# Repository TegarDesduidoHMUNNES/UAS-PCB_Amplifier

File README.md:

-Tegar Desduido Hasbing Mulia
--2305110008
---Teknik Komputer 2023
----Matkul Elektronika-UAS

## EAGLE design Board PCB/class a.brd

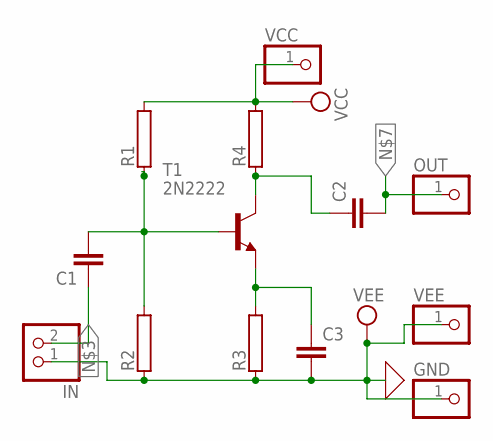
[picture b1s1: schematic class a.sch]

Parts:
C1, C2, C3: C2,5-3; C2.5-3
GND: PINHD-1X1; 1X01
IN: PINHD-1X2; 1X02
OUT: PINHD-1X1; 1X01
R1, R2, R3, R4: RAC01; AC01
T1: 2N2222; TO18
VCC: PINHD-1X1; 1X01
VEE: PINHD-1X1; 1X01

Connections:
unnamed: C1.2, R1.1, R2.2, T1.2 (B)
unnamed: C2.1, R4.1, T1.3 (C)
unnamed: C1.1, IN.2
unnamed: C3.1, R3.2, T1.1 (E)
unnamed: C2.2, OUT.1
VCC: R1.2, R4.2, VCC.1
VEE: C3.2, GND.1, IN.1, R2.1, R3.1, VEE.1

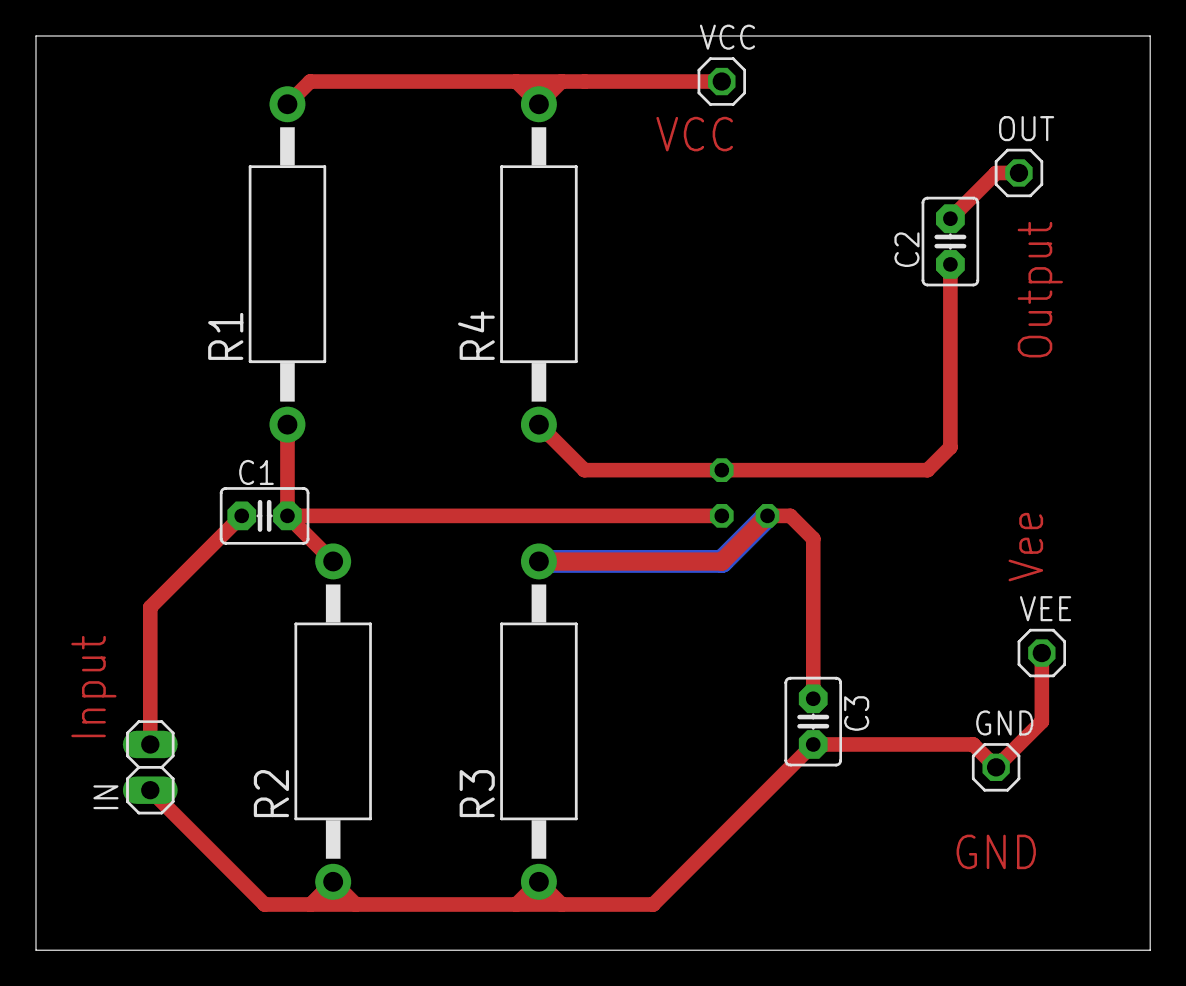
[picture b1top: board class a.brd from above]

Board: 2 copper layers, 61.9 x 50.8 mm, 13 parts (1 on the bottom side), 7 nets.

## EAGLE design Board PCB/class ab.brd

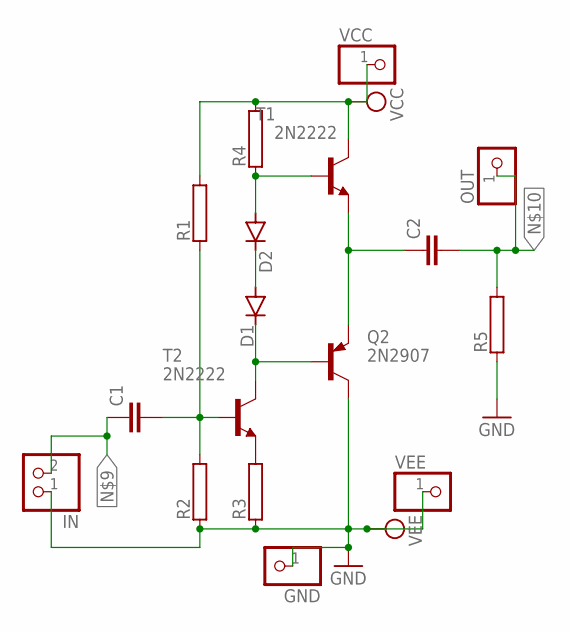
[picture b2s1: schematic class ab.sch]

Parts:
C1, C2: C2,5-3; C2.5-3
D1, D2: 1N4148DO35-7; DO35-7
GND: PINHD-1X1; 1X01
IN: PINHD-1X2; 1X02
OUT: PINHD-1X1; 1X01
Q2: 2N2907; TO18
R1, R2, R3, R4, R5: RAC01; AC01
T1, T2: 2N2222; TO18
VCC: PINHD-1X1; 1X01
VEE: PINHD-1X1; 1X01

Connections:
GND: GND.1, IN.1, Q2.3 (C), R2.1, R3.1, R5.1, VEE.1
unnamed: C1.2, R1.1, R2.2, T2.2 (B)
unnamed: D1.C, Q2.2 (B), T2.3 (C)
unnamed: D1.A, D2.C
unnamed: D2.A, R4.1, T1.2 (B)
unnamed: R3.2, T2.1 (E)
unnamed: C2.1, Q2.1 (E), T1.1 (E)
unnamed: C1.1, IN.2
unnamed: C2.2, OUT.1, R5.2
VCC: R1.2, R4.2, T1.3 (C), VCC.1

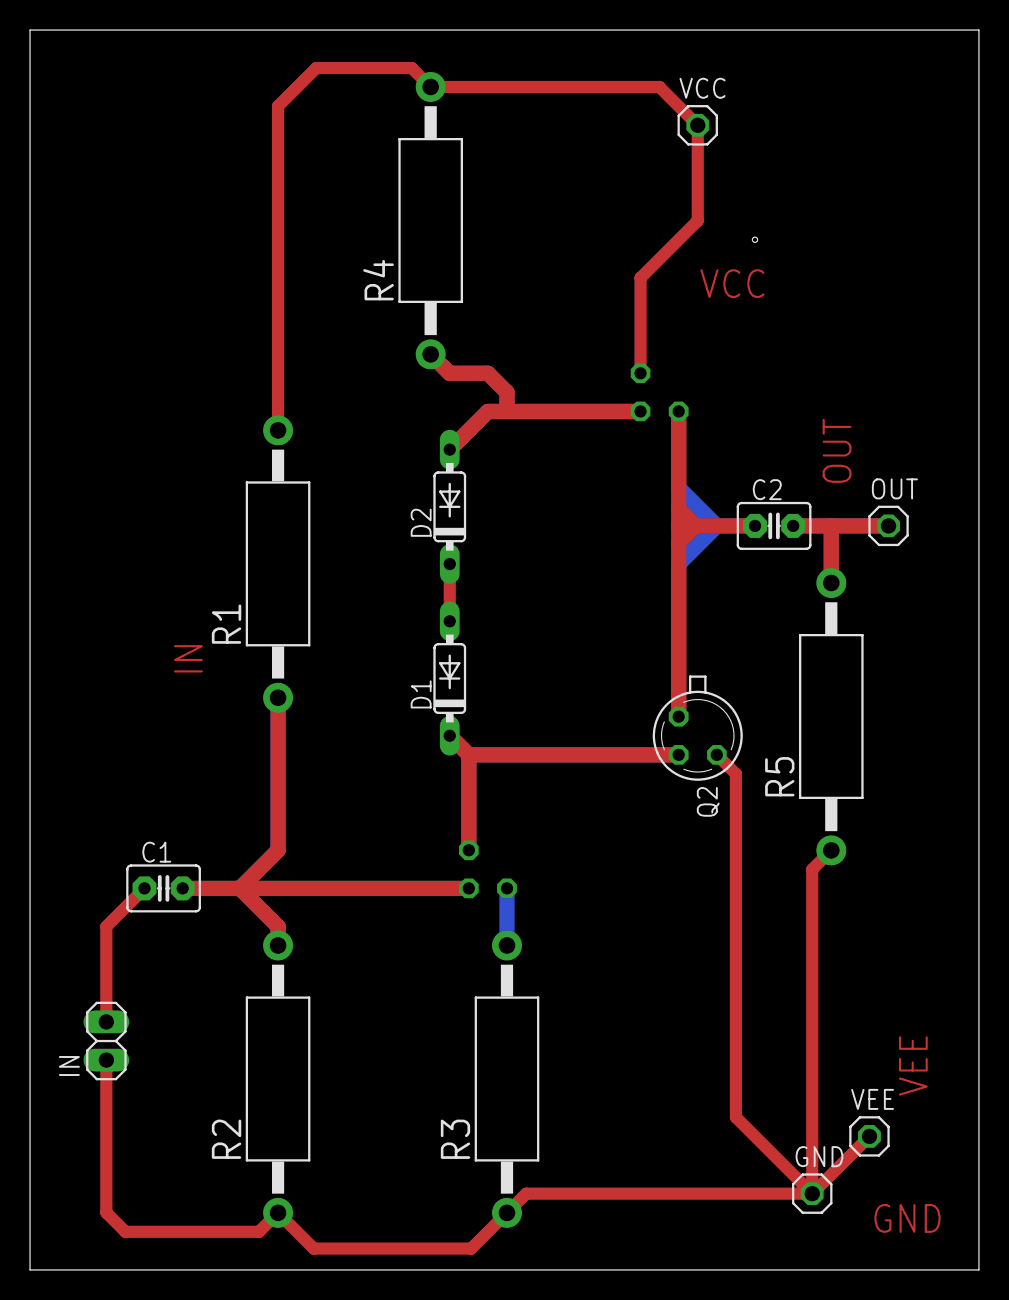
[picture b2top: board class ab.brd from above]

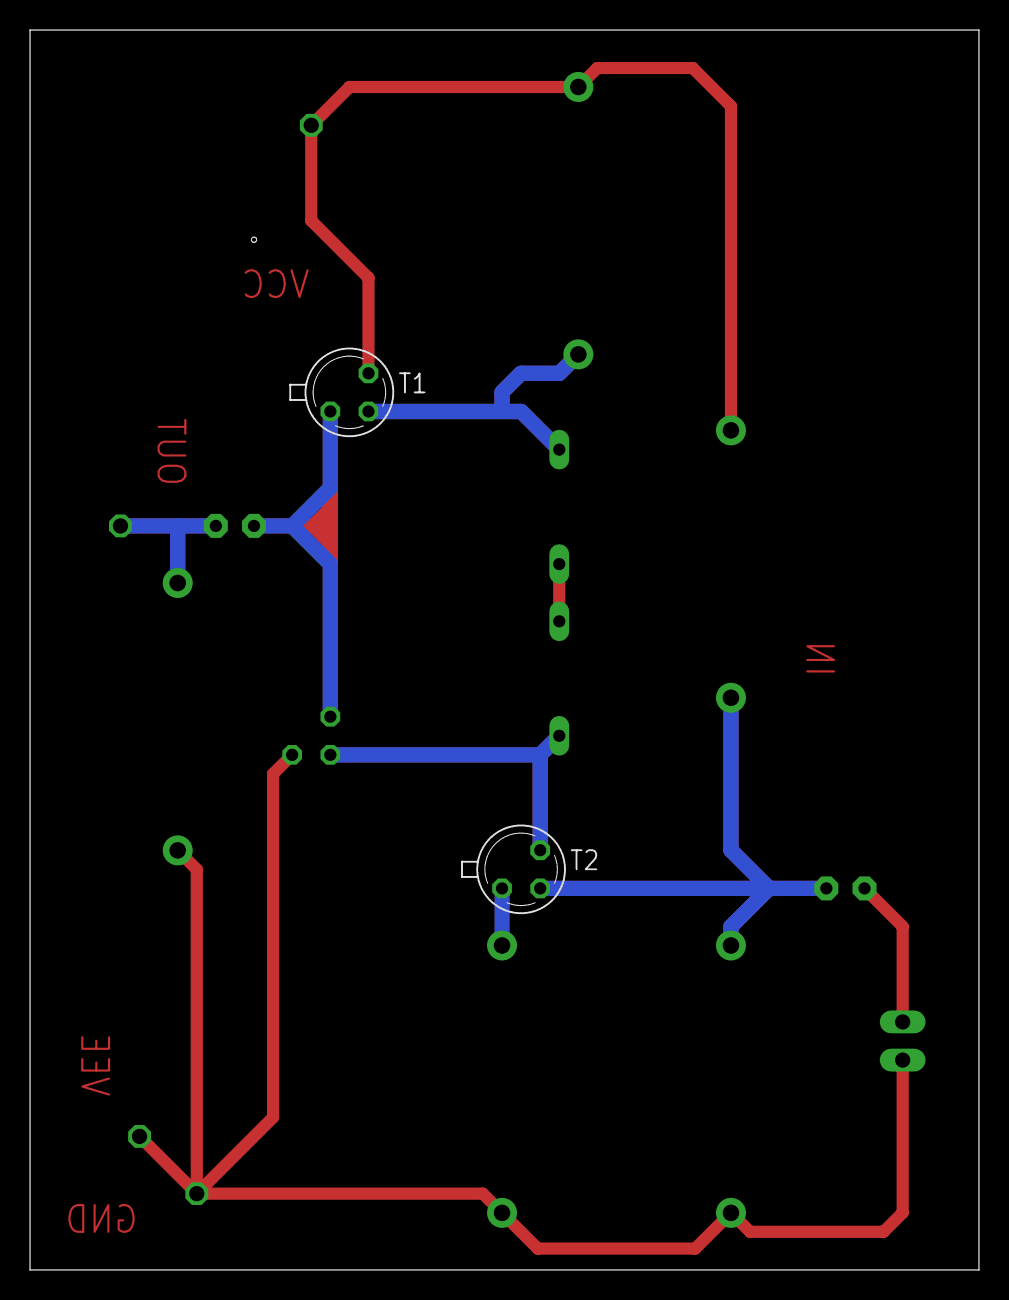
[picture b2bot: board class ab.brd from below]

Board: 2 copper layers, 63.2 x 82.5 mm, 17 parts (2 on the bottom side), 10 nets.

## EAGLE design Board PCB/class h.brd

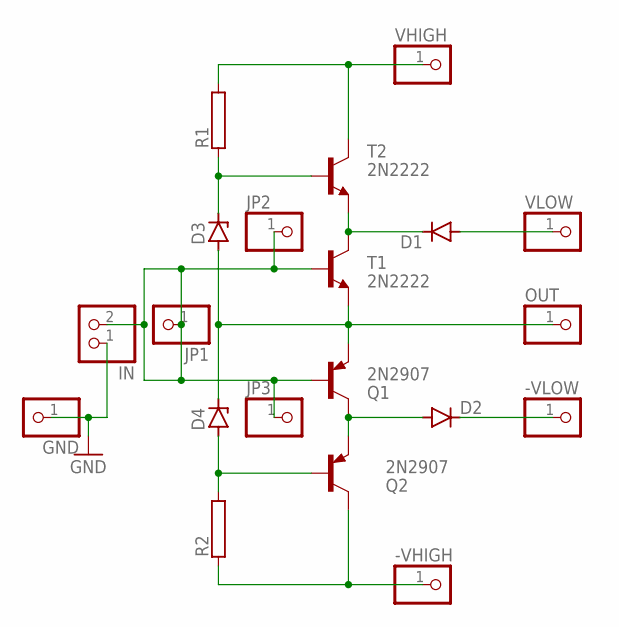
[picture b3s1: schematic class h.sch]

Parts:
-VHIGH: PINHD-1X1; 1X01
-VLOW: PINHD-1X1; 1X01
D1, D2: 1N4148DO35-7; DO35-7
D3, D4: 1N4728; DO41Z10
GND: PINHD-1X1; 1X01
IN: PINHD-1X2; 1X02
JP1, JP2, JP3: PINHD-1X1; 1X01
OUT: PINHD-1X1; 1X01
Q1, Q2: 2N2907; TO18
R1, R2: RAC01; AC01
T1, T2: 2N2222; TO18
VHIGH: PINHD-1X1; 1X01
VLOW: PINHD-1X1; 1X01

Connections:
GND: GND.1, IN.1
unnamed: D3.C, R1.1, T2.2 (B)
unnamed: IN.2, JP1.1, JP2.1, JP3.1, Q1.2 (B), T1.2 (B)
unnamed: D1.A, VLOW.1
unnamed: D3.A, D4.C, OUT.1, Q1.1 (E), T1.1 (E)
unnamed: D1.C, T1.3 (C), T2.1 (E)
unnamed: D2.A, Q1.3 (C), Q2.1 (E)
unnamed: -VHIGH.1, Q2.3 (C), R2.1
unnamed: R1.2, T2.3 (C), VHIGH.1
unnamed: D4.A, Q2.2 (B), R2.2
unnamed: -VLOW.1, D2.C

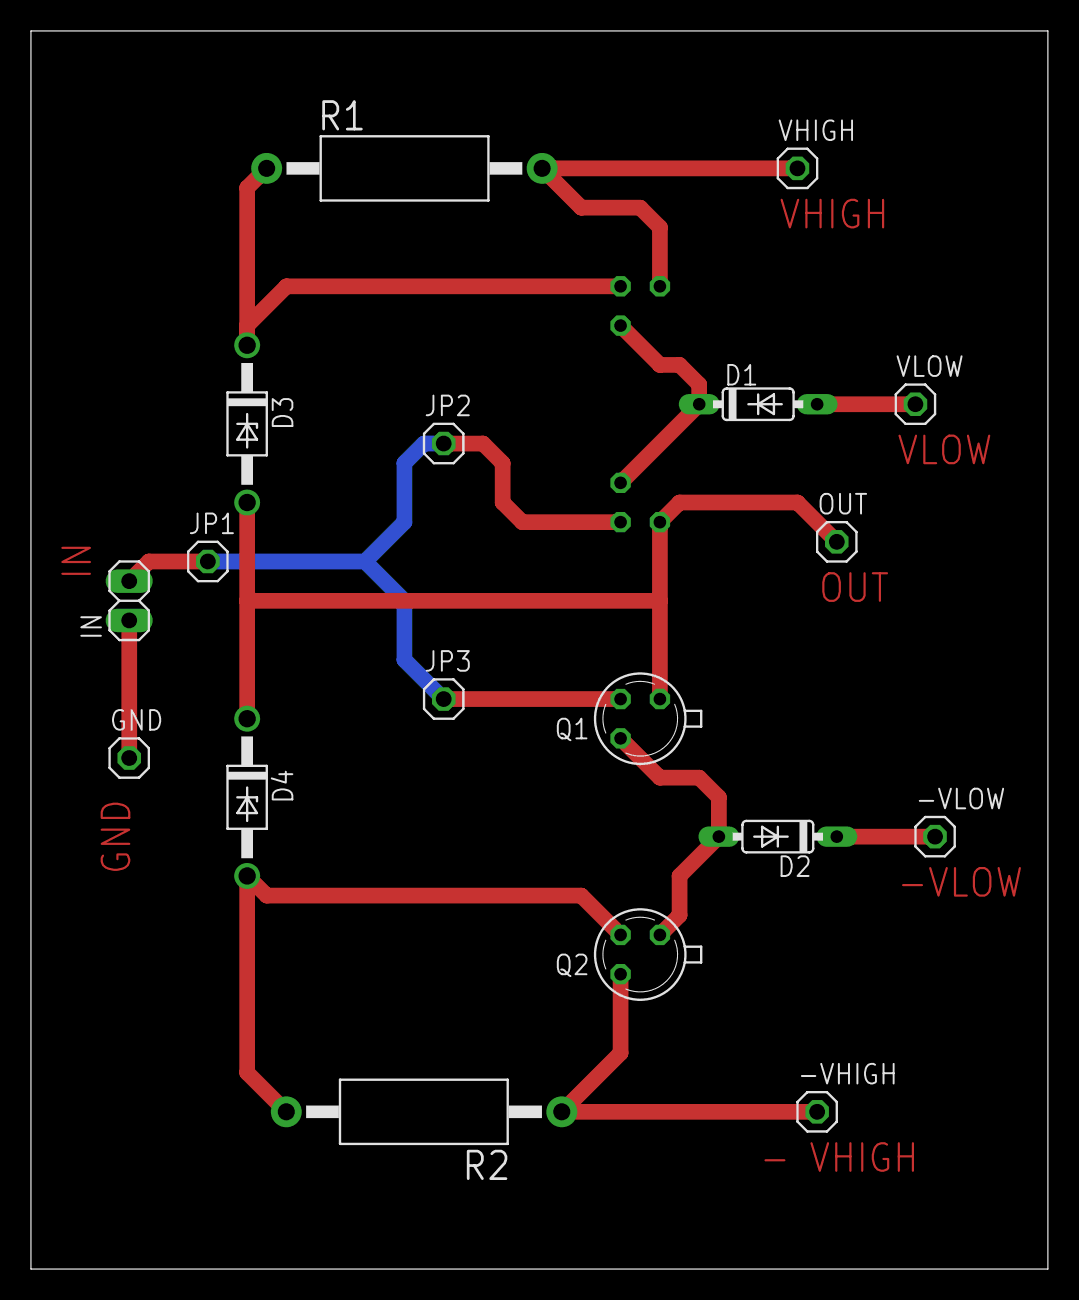
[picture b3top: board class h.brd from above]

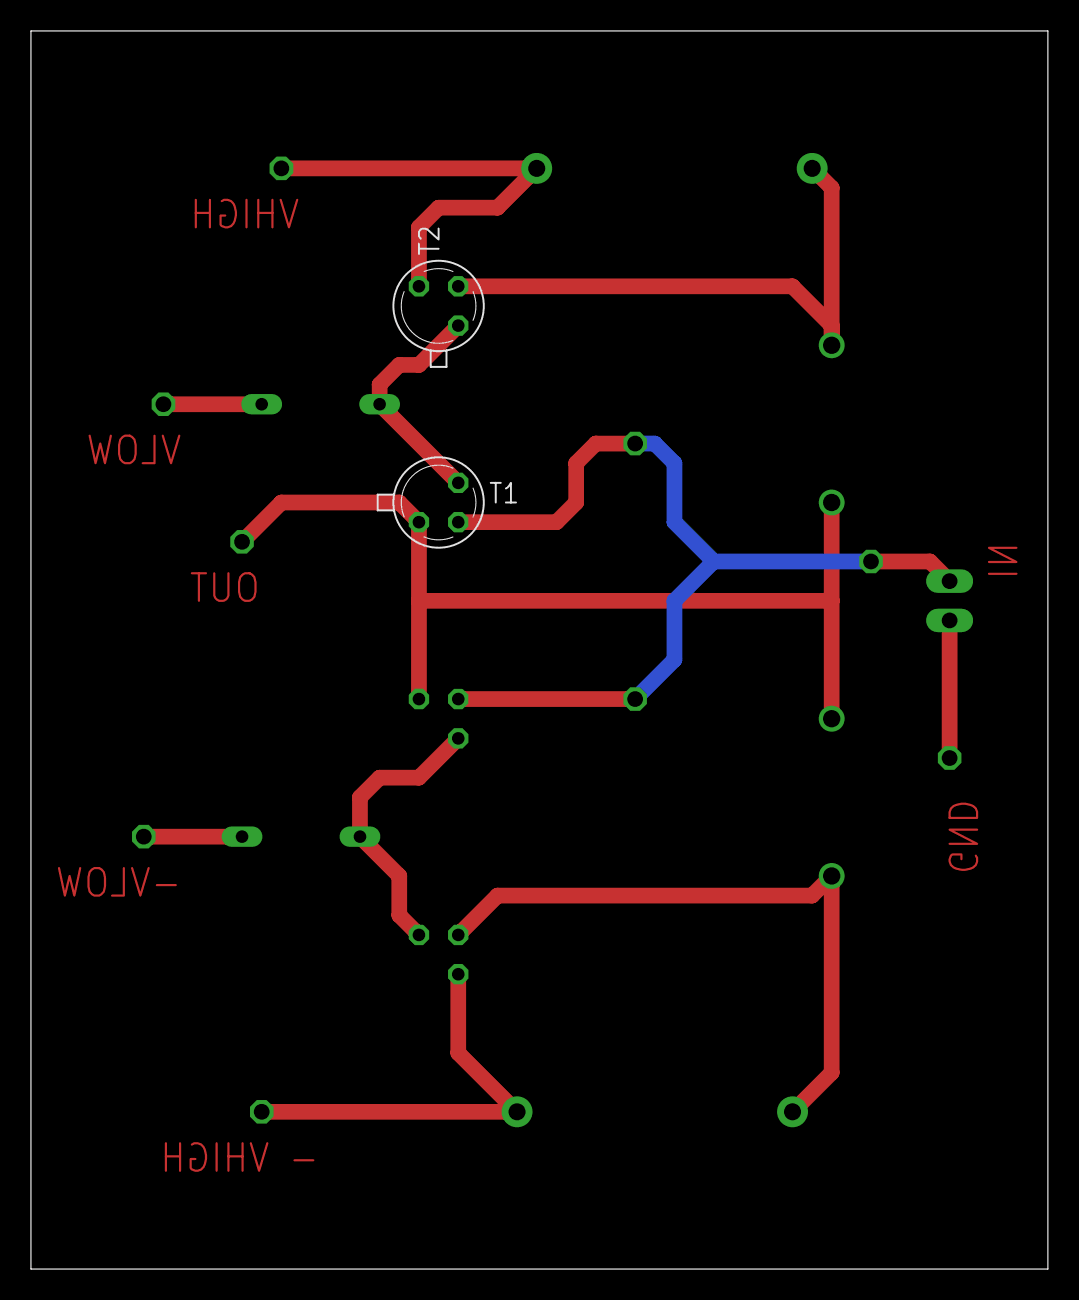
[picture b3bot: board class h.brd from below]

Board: 2 copper layers, 65.7 x 80.0 mm, 20 parts (2 on the bottom side), 11 nets.

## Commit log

2024-06-12 Create Class A Amp
2024-06-12 Create DelBr
2024-06-12 Create l
